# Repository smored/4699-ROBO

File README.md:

Computer Vision Target Shooting Robot
=====================================

Objective:
----------
"The design project is to develop a robot that competes in an [arena](https://cdn.discordapp.com/attachments/817281300821049352/977007824553009233/unknown.png). The robot begins in a start box, and when driving forward breaks an IR beam to start the timer. The robot must then strike 4 contact plates and continue on to the finish box where the timer is stopped. The arena must be completed in two different modes, 1) teleoperation where the user drives via commands and images over TCP/IP and 2) autonomous mode where the robot solves the arena without human intervention."

Our Solution:
-------------
We decided to base our design around two [NEMA 17](https://www.amazon.ca/gp/product/B09N3NRTW9/ref=ppx_yo_dt_b_asin_title_o06_s01?ie=UTF8&psc=1) stepper motors using respective [L298N](https://www.amazon.ca/gp/product/B00XAGRQTO/ref=ppx_yo_dt_b_asin_title_o07_s00?ie=UTF8&psc=1) driver circuit boards and a [Teensy 4.0](https://www.amazon.ca/Teensy-4-0-with-Pins/dp/B08259KDHY/ref=sr_1_1?crid=2YYR6ATL3VK35&keywords=teensy+4.0&qid=1653007497&sprefix=teensy+4+0%2Caps%2C522&sr=8-1) to interface the motors to the [Raspbery Pi 4b](https://www.amazon.ca/s?k=rasberry+pi+4+b&crid=1HV9MO5X30TG&sprefix=rasb%2Caps%2C238&ref=nb_sb_ss_ts-doa-p_1_4). We would use two [ultrasonic sensors](https://www.sparkfun.com/products/15569) for positional alignment, a [servo](https://www.amazon.ca/gp/product/B07VJG5QTJ/ref=ppx_yo_dt_b_asin_title_o05_s00?ie=UTF8&psc=1) for turret aiming, a [servo](https://www.amazon.ca/gp/product/B07KR24YX8/ref=ppx_yo_dt_b_asin_title_o03_s00?ie=UTF8&psc=1) for firing at the targets, and finally a [pi camera](https://www.amazon.ca/Keyestudio-Camera-Module-5MP-Raspberry/dp/B073RCXGQS/ref=sr_1_5?crid=10T4SHGENUO6L&keywords=pi%2Bcamera&qid=1653007276&sprefix=p%2Caps%2C299&sr=8-5&th=1). We decided to split the main functionality of the robot into two parts: Driving (Teensy) and Detection (Raspberry Pi). There are two main reasons for this decision, first we wanted to unload as much possible processing from the raspberry pi so that our computer vision algorithm could run faster, and second it allowed us to completely isolate our workloads into two seperate entities, and thus we could work asychronously. 

For Auto mode our algorithm was based around a state machine, each state being defined as a portion of the arena. The Teensy would drive the motors to the first location, wait for feedback from the Pi on when the target was successfully hit, then move to the second target, and so on. The Pi would grab the state of each target from a server hosted by the arena over TCP/IP, and pass that information onto the Teensy via UART. 

The method used to aim the cannon was to use the pi camera to scan for ArUCO QR codes, using that information encoded into screenspace, determine whether the target was on the left or right of the centre of the camera. If the ArUCO was in the centre, it would fire the cannon.

In manual driving mode, the user would input keypresses into a windows client on a laptop that communicated with the Pi over TCP/IP. The client additionally fetched a camera feed from the arena, and a camera feed from the Pi to enable the user to fully drive the unit without line of sight to the arena.

Media:
------

[More Robot](https://photos.app.goo.gl/skK17sW5vWhY1REk8)

Credits:
-------
**Kurt Querengesser**

Author of PI code and Lead Parts Designer

**Michael Andrews**

Author of Microcontroller Code and Lead PCB Designer

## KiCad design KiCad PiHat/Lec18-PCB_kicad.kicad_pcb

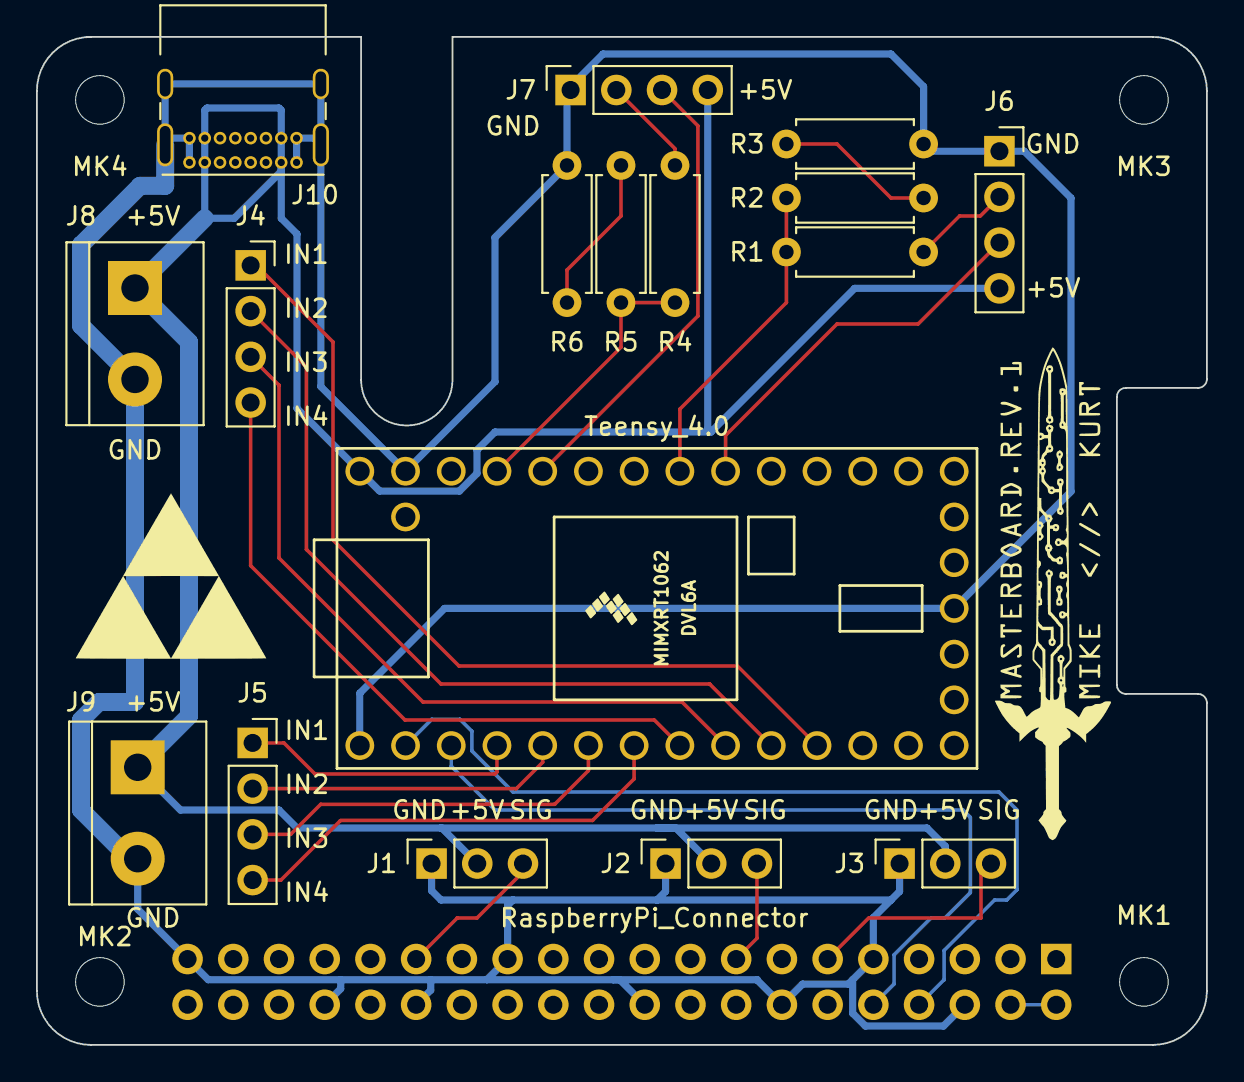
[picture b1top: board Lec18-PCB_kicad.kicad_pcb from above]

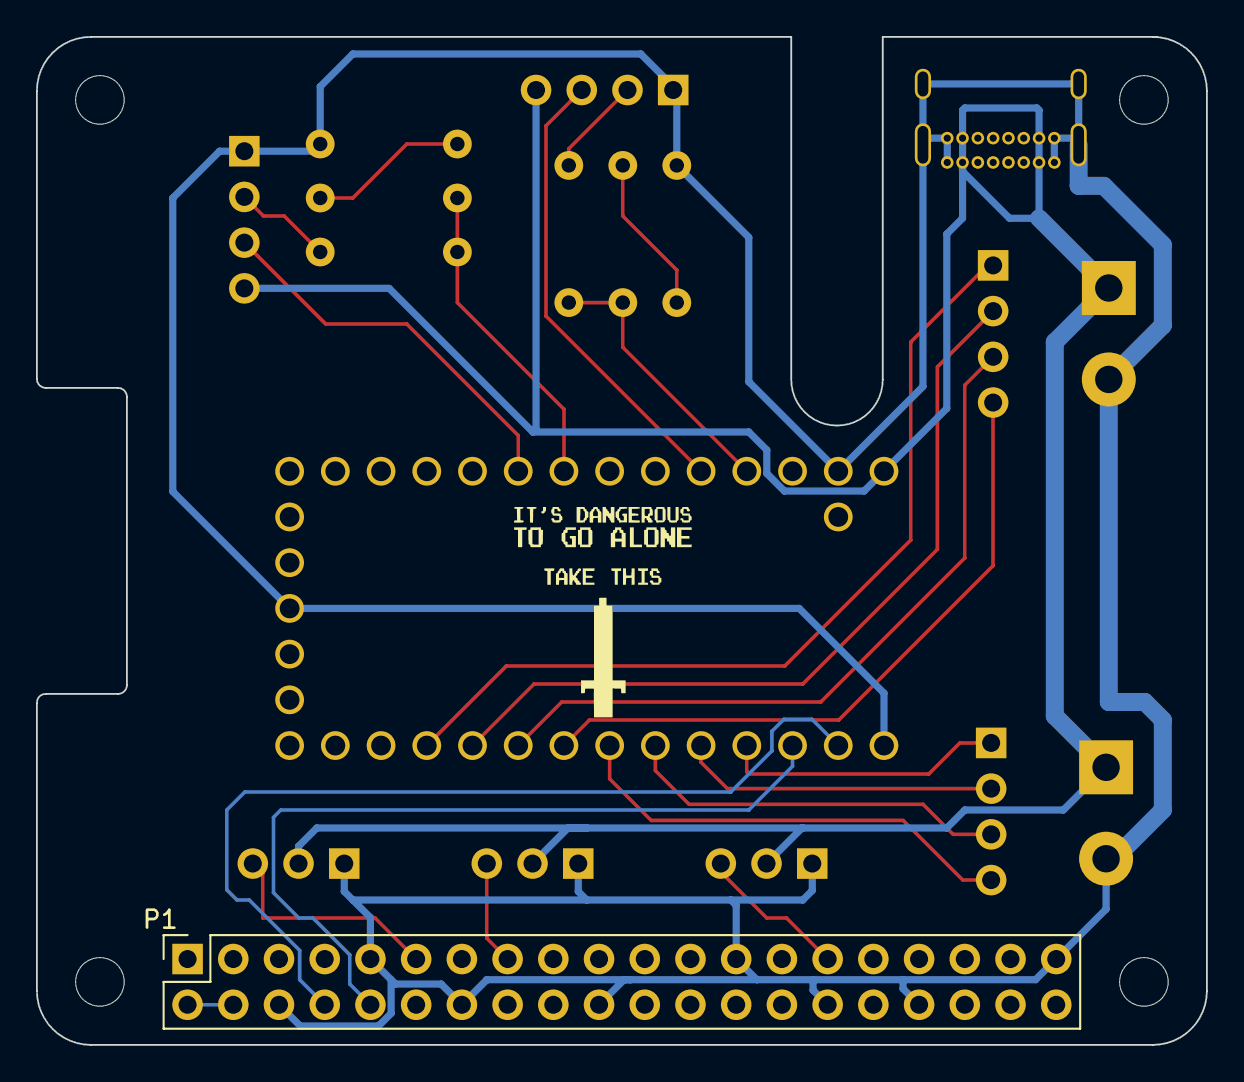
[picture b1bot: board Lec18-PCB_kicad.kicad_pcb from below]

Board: 2 copper layers, 65.0 x 56.0 mm, 25 parts (2 on the bottom side), 25 nets.

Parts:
A1: Teensy_4.0; Teensy40
J1: Servo_BEEG; PinSocket_1x03_P2.54mm_Vertical
J2: Servo_SHOOT; PinSocket_1x03_P2.54mm_Vertical
J3: Servo_EXTRA; PinSocket_1x03_P2.54mm_Vertical
J4: Motor_Driver_Left; PinSocket_1x04_P2.54mm_Vertical
J5: Motor_Driver_Right; PinSocket_1x04_P2.54mm_Vertical
J6: Ultrasonic_Front; PinSocket_1x04_P2.54mm_Vertical
J7: Ultrasonic_Left; PinSocket_1x04_P2.54mm_Vertical
J8: Motor_Power_Left; TerminalBlock_bornier-2_P5.08mm
J9: Motor_Power_Right; TerminalBlock_bornier-2_P5.08mm
J10: USB_C_Receptacle_USB2.0; USB_C_Receptacle_GCT_USB4085
Logo: LOGO; Masterboard_Logo
MK1, MK2, MK3, MK4: M2.5; MountingHole_2.7mm_M2.5
P1: RaspberryPi_Connector; PinSocket_2x20_P2.54mm_Vertical
R1, R2, R3, R4, R5, R6: 1k; R_Axial_DIN0207_L6.3mm_D2.5mm_P7.62mm_Horizontal
Triforce: LOGO; Triforce
image: LOGO; Dangerous

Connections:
+5V: A1.33 (VIN), J1.2, J2.2, J3.2, J6.4, J7.4, J8.1, J9.1, J10.A4 (VBUS), J10.A9 (VBUS), J10.B4 (VBUS), J10.B9 (VBUS)
/GPIO5: J1.3, P1.29
/GPIO17(GEN0): J3.3, P1.11
/GPIO22(GEN3): J2.3, P1.15
/IN1(MOTOR_LEFT): A1.11 (9_OUT1C), J4.1
/IN1(MOTOR_RIGHT): A1.4 (2_OUT2), J5.1
/IN2(MOTOR_LEFT): A1.10 (8_TX2_IN1), J4.2
/IN2(MOTOR_RIGHT): A1.5 (3_LRCLK2), J5.2
/IN3(MOTOR_LEFT): A1.9 (7_RX2_OUT1A), J4.3
/IN3(MOTOR_RIGHT): A1.6 (4_BCLK2), J5.3
/IN4(MOTOR_LEFT): A1.8 (6_OUT1D), J4.4
/IN4(MOTOR_RIGHT): A1.7 (5_IN2), J5.4
/PI_to_Teensy: A1.2 (0_RX1_CRX2_CS1), P1.8
/Teensy_to_PI: A1.3 (1_TX1_CTX2_MISO1), P1.10
/Ultrasonic_Front_Echo: A1.26 (19_A5_SCL0), R1.2, R2.1
/Ultrasonic_Front_Trig: A1.25 (18_A4_SDA0), J6.3
/Ultrasonic_Left_Echo: A1.30 (23_A9_CRX1_MCLK1), R4.2, R5.1
/Ultrasonic_Left_Trig: A1.29 (22_A8_CTX1), J7.3
GND: A1.1 (GND), A1.17 (GND), A1.32 (GND), J1.1, J2.1, J3.1, J6.1, J7.1, J8.2, J9.2, J10.A1 (GND), J10.A12 (GND), J10.B1 (GND), J10.B12 (GND), J10.S1 (SHIELD), P1.6, P1.9, P1.14, P1.20, P1.25, P1.30, P1.34, P1.39, R3.2, R6.2
unnamed: J7.2, R4.1
unnamed: P1.1, P1.17
unnamed: P1.2, P1.4
unnamed: J6.2, R1.1
unnamed: R2.2, R3.1
unnamed: R5.2, R6.1

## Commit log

2022-04-12 created repo. unfinished chassis model.
2022-04-12 first chassis prototype finished and printing
    mainly just a test to see if i can fit battery and pi in
2022-04-27 chassis rv2 modelled with accessories
    scaled up the given chassis model to accommodate more board real estate. added ultrasonic sensors and turret module as well as pi hat and motors. not yet finished since some spaces overlap
2022-04-27 Add KiCad PiHat Files
2022-04-28 rearranged whole chassis (r3) working on battery holder
2022-04-28 Ongoing work
    Continued work on schematic and PCB
2022-04-28 Finished Schematic
    Schematic finished. Sanity check and routing coming next
2022-04-28 3 chassis parts finished
    mainboard, battery holder, and servo holder ready for printing
2022-04-28 routing complete
2022-04-28 Attempted to add logo
2022-04-28 PCB complete with logos and graphics
    PCB work complete. Going to speak with instructor to make sure all parameters are correct before sending out to have the pcb made.
2022-04-28 pushing STLs for printing
2022-04-28 chassis stiffened and motor mounts improved
2022-04-28 PCB Finalized
2022-04-28 File system cleanup
2022-04-28 raft added to chassis
2022-04-28 rearranged folders
2022-04-29 started coding pi program
2022-05-02 Continued work on drive system
2022-05-03 worked on the ArUco detection code today, wasnt able to get multithreading working and servo control is NYI
2022-05-03 Continued work on the driving
2022-05-03 dragger added to chassis
    ;)
2022-05-03 updated servo mount
    added wire hole
2022-05-04 not sure tbh
2022-05-04 basic servo movement left and right working imshow not displaying to screen for some reason but tracking is still working
2022-05-05 basic Proportional control working with servo
2022-05-05 overhauled launcher mount design
    connects the BEEG servo to launcher. includes an adjustable angle jig
2022-05-06 Drive algorithm work
2022-05-06 made first revision of wheel
2022-05-06 wheel
2022-05-06 wheel revision 2
2022-05-07 final commit before I attempt PID integration
2022-05-07 Driving to target 3 complete
2022-05-09 Code for driving done
    Needs lots of tweaking with the numbers. Basic functioning working now.
2022-05-10 imshow() now properly showing to screen, new classes added for communcation and handling servo
2022-05-10 servo instantiation implemented and used for both turret and launcher
2022-05-11 new wheel design
2022-05-11 wheel tweaks
2022-05-11 I done it again
2022-05-12 added cvui settings window for testing, implemented uart prototype serial communication is a WIP but has been started. added some new members, threads moved into runLoop() instead of constructor. bun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
2022-05-13 wheel modified
2022-05-13 latest version for kurt to use
2022-05-15 chages to BEEGDrive for serial com
2022-05-15 laptop client added
2022-05-15 added the rest of the crap
2022-05-15 hnnnnnn
2022-05-15 laptop client updated
2022-05-15 made serial communication work with teensy also communicates with laptop client which will send state data
2022-05-17 cleaning up repo
2022-05-17 updated ID detection for consistency and other code improvements
2022-05-18 Final Auto Version of BEEGDrive
2022-05-18 sub 40 second run achieved with this code reworked state machine and tweaked delays as well as other small changes
2022-05-19 Working manual controls
2022-05-19 communcating with teensy for manual over gpio
2022-05-19 manual implementention finished
2022-05-19 Final Teensy code done
2022-05-19 cleaning up repo and final code push
2022-05-20 adding readme and cleaning up
